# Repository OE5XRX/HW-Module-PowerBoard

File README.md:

# HW-Module-PowerBoard

## License

This project is licensed under [CERN-OHL-S-2.0](https://choosealicense.com/licenses/cern-ohl-s-2.0/).

## Badges

<br>
<br>
<br>
<br>
<br>

## Contact

OE5XRX Amateur Radio Club<br>
🌐 https://oe5xrx.org<br>
✉️ info@oe5xrx.org<br>

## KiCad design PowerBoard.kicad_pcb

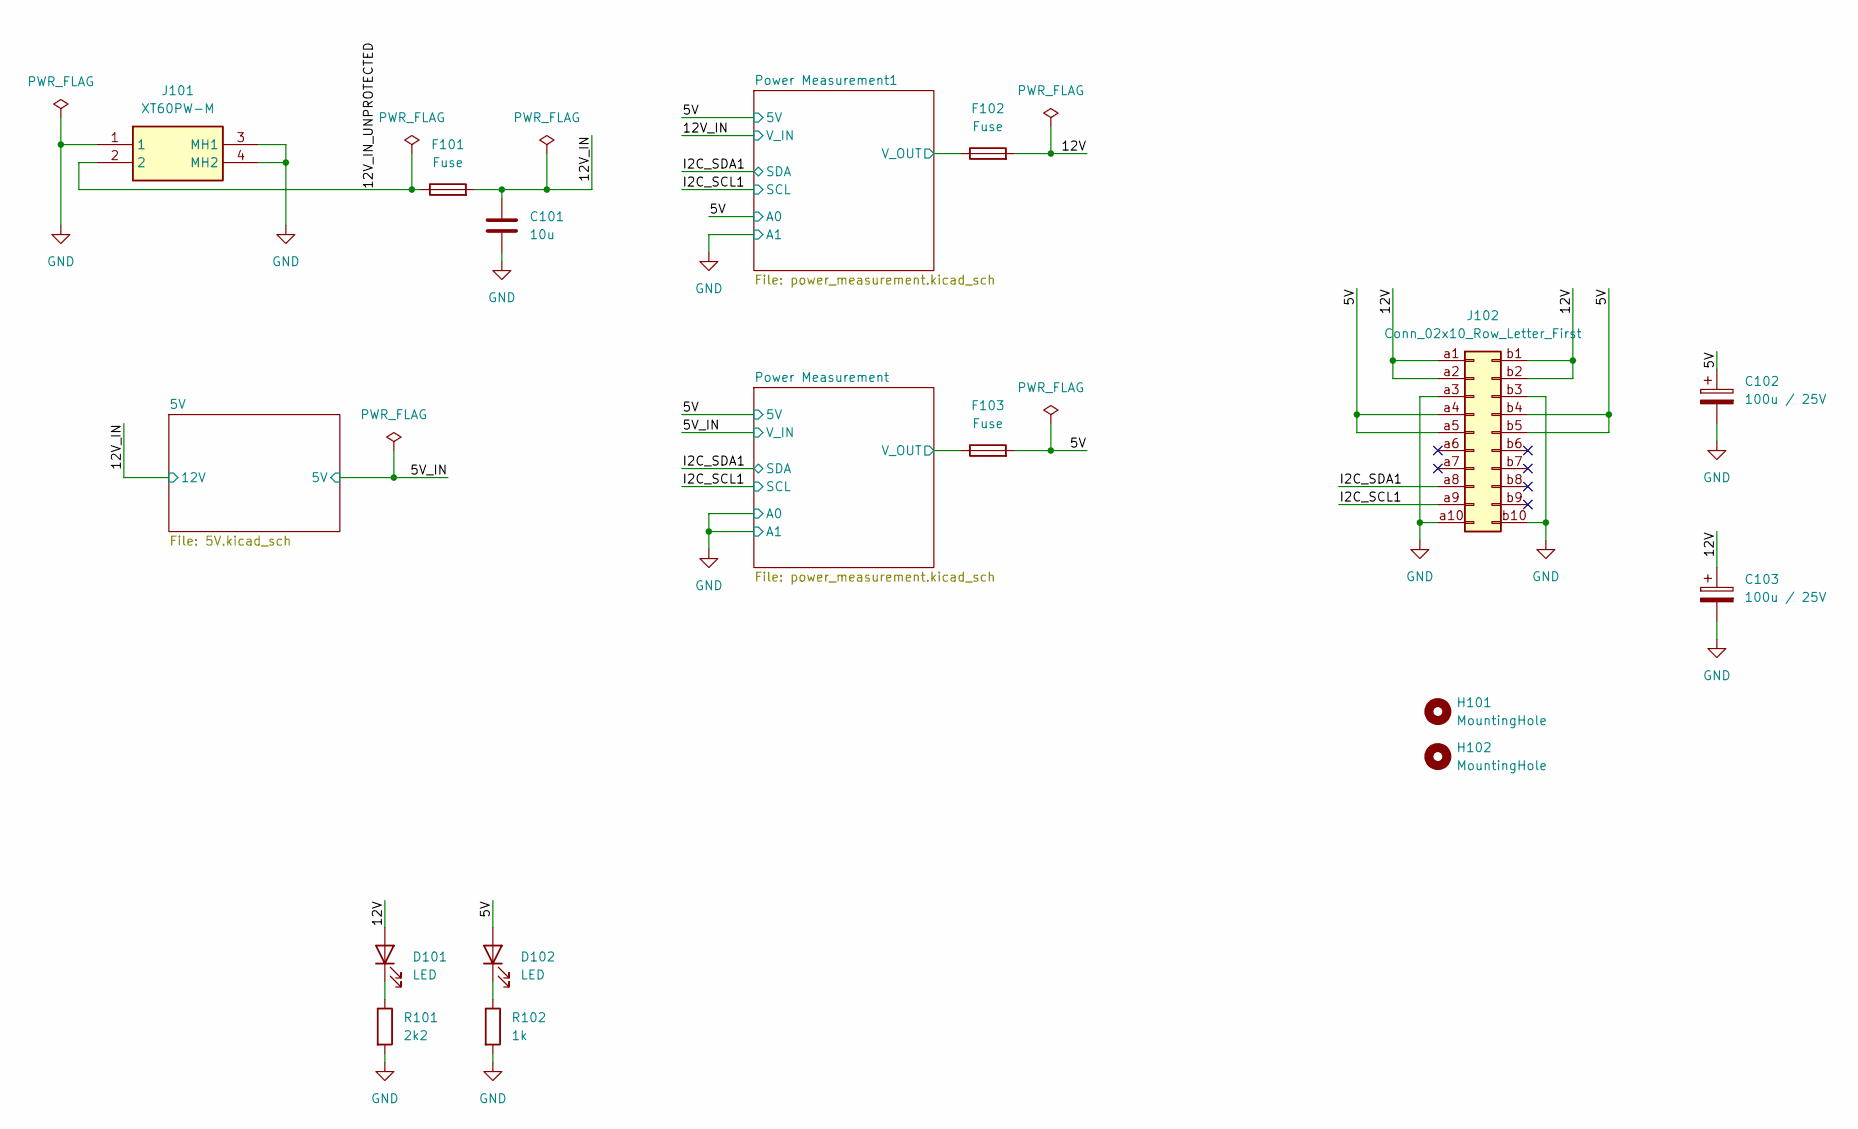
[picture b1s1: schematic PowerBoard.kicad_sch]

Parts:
C101: 10u; C_1206_3216Metric; LCSC C13585
C102, C103: 100u / 25V; CP_EIA-7343-43_Kemet-X; LCSC C132558
D101, D102: LED; LED_0805_2012Metric; LCSC C84256
F101, F102, F103: Fuse; FUSE_01530007Z; MOUSER 576-01530007Z
H101, H102: MountingHole; MountingHole_3.2mm_M3
J101: XT60PW-M; XT60PWM
J102: Conn_02x10_Row_Letter_First; PCN10C-20S-2.54DS; MOUSER 798-PCN10C20S254DS72
R101: 2k2; R_0805_2012Metric; LCSC C17520
R102: 1k; R_0805_2012Metric; LCSC C17513

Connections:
/5V: C102.1, D102.2 (A), F103.2, J102.a4, J102.a5, J102.b4, J102.b5; also elsewhere on the board
/12V: C103.1, D101.2 (A), F102.2, J102.a1, J102.a2, J102.b1, J102.b2
/12V_IN: C101.1, F101.2; also elsewhere on the board
/12V_IN_UNPROTECTED: F101.1, J101.2
/I2C_SCL1: J102.a9; also elsewhere on the board
/I2C_SDA1: J102.a8; also elsewhere on the board
/Power Measurement1/V_OUT: F102.1; also elsewhere on the board
/Power Measurement/V_OUT: F103.1; also elsewhere on the board
GND: C101.2, C102.2, C103.2, J101.1, J101.3 (MH1), J101.4 (MH2), J102.a3, J102.a10, J102.b3, J102.b10, R101.2, R102.2; also elsewhere on the board
unnamed: D101.1 (K), R101.1
unnamed: D102.1 (K), R102.1

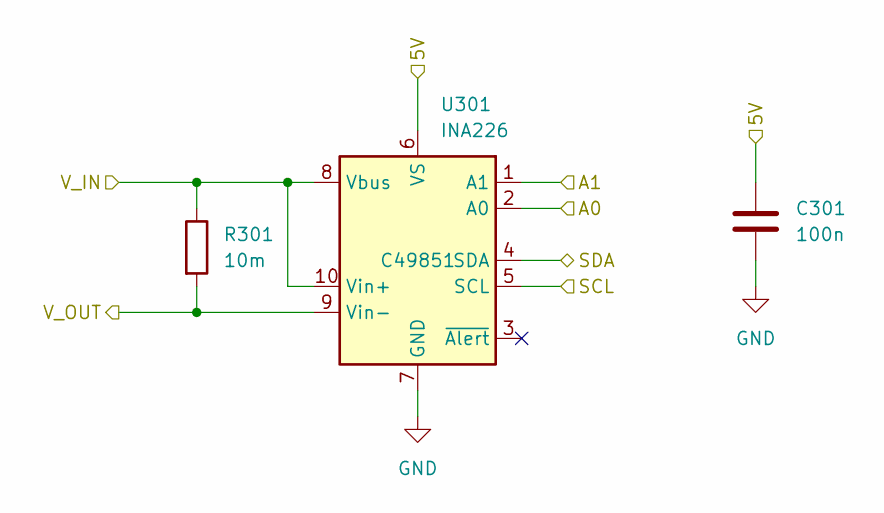
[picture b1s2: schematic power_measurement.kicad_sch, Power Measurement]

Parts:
C301: 100n; C_0805_2012Metric; LCSC C28233
R301: 10m; R_2512_6332Metric; MOUSER 652-CRF2512FZR010ELF
U301: INA226; VSSOP-10_3x3mm_P0.5mm; LCSC C49851

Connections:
/5V: C301.1, U301.6 (VS); also elsewhere on the board
/5V_IN: R301.1, U301.8 (Vbus), U301.10 (Vin+); also elsewhere on the board
/I2C_SCL1: U301.5 (SCL); also elsewhere on the board
/I2C_SDA1: U301.4 (SDA); also elsewhere on the board
/Power Measurement/V_OUT: R301.2, U301.9 (Vin-); also elsewhere on the board
GND: C301.2, U301.1 (A1), U301.2 (A0), U301.7 (GND); also elsewhere on the board

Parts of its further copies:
C401: 100n; C_0805_2012Metric; LCSC C28233
R401: 10m; R_2512_6332Metric; MOUSER 652-CRF2512FZR010ELF
U401: INA226; VSSOP-10_3x3mm_P0.5mm; LCSC C49851

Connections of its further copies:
/5V: C401.1, U401.2 (A0), U401.6 (VS); also elsewhere on the board
/12V_IN: R401.1, U401.8 (Vbus), U401.10 (Vin+); also elsewhere on the board
/I2C_SCL1: U401.5 (SCL); also elsewhere on the board
/I2C_SDA1: U401.4 (SDA); also elsewhere on the board
/Power Measurement1/V_OUT: R401.2, U401.9 (Vin-); also elsewhere on the board
GND: C401.2, U401.1 (A1), U401.7 (GND); also elsewhere on the board

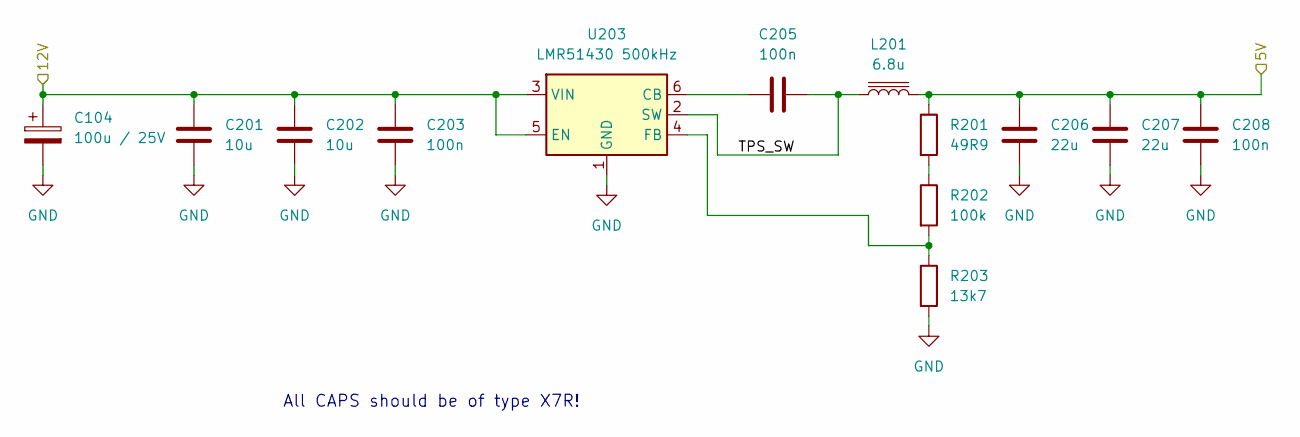
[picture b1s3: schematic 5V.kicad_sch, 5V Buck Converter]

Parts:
C104: 100u / 25V; CP_EIA-7343-43_Kemet-X; LCSC C132558
C201, C202: 10u; C_1206_3216Metric; LCSC C13585
C203, C205, C208: 100n; C_0805_2012Metric; LCSC C28233
C206, C207: 22u; C_1206_3216Metric; LCSC C12891
L201: 6.8u; WE-XHMI_6060; MOUSER 710-74439346068
R201: 49R9; R_0805_2012Metric; MOUSER 667-ERA-6AED49R9V
R202: 100k; R_0805_2012Metric; MOUSER 603-RC0805JR-07100KL
R203: 13k7; R_0805_2012Metric; MOUSER 652-CR0805FX-1372ELF
U203: LMR51430 500kHz; SOT-23-6; MOUSER 595-LMR51430XDDCR

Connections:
/5V/TPS_SW: C205.2, L201.1, U203.2 (SW)
/5V_IN: C206.2, C207.2, C208.2, L201.2, R201.1; also elsewhere on the board
/12V_IN: C104.1, C201.1, C202.1, C203.1, U203.3 (VIN), U203.5 (EN); also elsewhere on the board
GND: C104.2, C201.2, C202.2, C203.2, C206.1, C207.1, C208.1, R203.2, U203.1 (GND); also elsewhere on the board
unnamed: R201.2, R202.1
unnamed: C205.1, U203.6 (CB)
unnamed: R202.2, R203.1, U203.4 (FB)

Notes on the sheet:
All CAPS should be of type X7R!

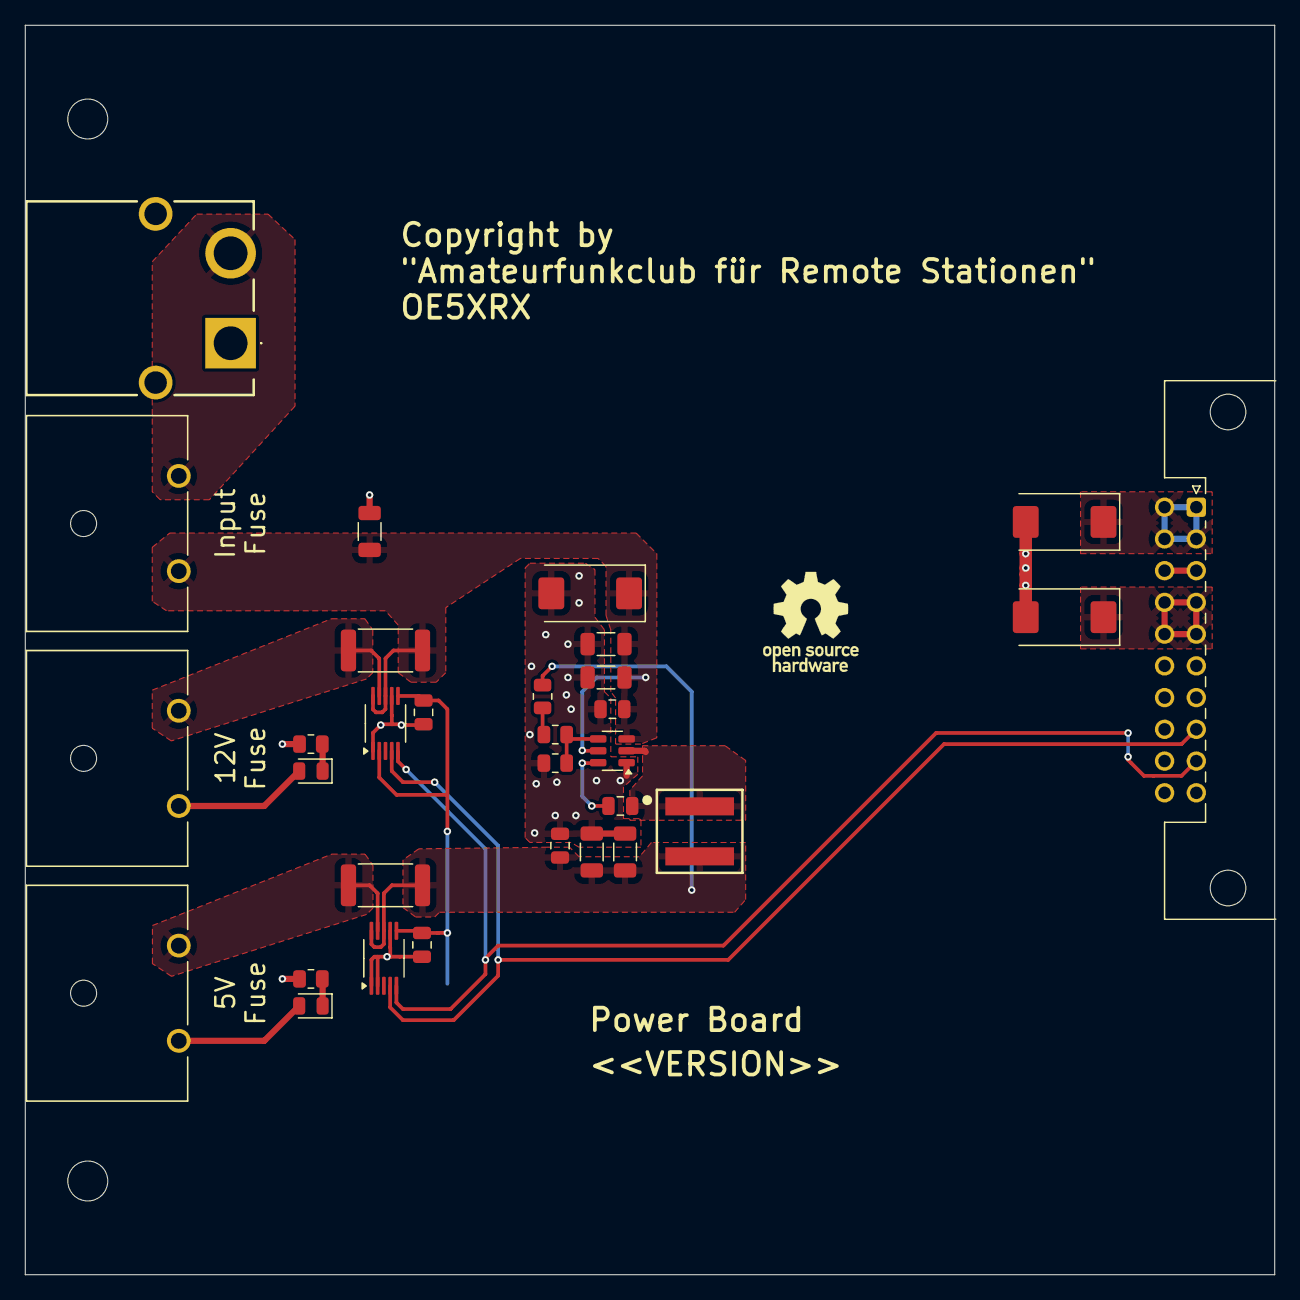
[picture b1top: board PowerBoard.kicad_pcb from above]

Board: 4 copper layers, 100.0 x 100.0 mm, 33 parts (0 on the bottom side), 16 nets.

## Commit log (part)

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2025-08-27 setup project
2025-08-28 fix path for external components
2025-08-28 fix index
2025-09-05 🔄 created local 'doc/_config.yml' from remote 'doc/_config.yml'
2025-09-05 🔄 created local 'doc/favicon.ico' from remote 'doc/favicon.ico'
2025-09-05 🔄 synced local '.github/workflows/create-debug-docs.yaml' with remote '.github/workflows/create-debug-docs.yaml'
2025-09-05 🔄 created local 'Gemfile' from remote 'Gemfile'
2025-09-05 Initial gh-pages commit
2025-09-05 Deploying to gh-pages from @ OE5XRX/HW-Module-PowerBoard@147898b77bba4ee0519c7e8ac76ab752825e97f0 🚀
2026-05-12 refactor(ci): replace workflows with HW-Module-CI thin wrappers
2026-05-12 chore(ci): delete files now provided by HW-Module-CI
2026-05-12 feat(docs): migrate index.md to Jekyll Liquid for output paths
2026-05-12 chore: ignore CI-generated doc/_data/project.yml
2026-05-12 rename(kicad): main.kicad_* → PowerBoard.kicad_*
2026-05-12 Deploying to gh-pages from @ OE5XRX/HW-Module-PowerBoard@edb127a616a350726788fd26fe98536b4139deb3 🚀
2026-05-12 Deploying to gh-pages from @ OE5XRX/HW-Module-PowerBoard@7f9eb825cc38174e3f664904ce8a251a15ba0276 🚀
2026-05-12 docs: rewrite Power index.md with overview, block-diagram, INA226 ranges, bringup
    Adds:
    - 1-sentence description front-matter (SEO + just-the-docs side-nav)
    - Übersicht paragraph linking to BusBoard and CM4Carrier
    - Mermaid block-diagram of the +12V/+5V flow
    - Versorgung table (input, +12V passthrough, +5V buck)
    - I²C measurement table with computed full-scale current and resolution
2026-05-12 ci: retrigger kibot-check with HW-Module-CI@main containing Docker-direct fix
2026-05-12 ci: retrigger after HW-Module-CI image pin to 1.8.5-7_k9.0.7
2026-05-12 Deploying to gh-pages from @ OE5XRX/HW-Module-PowerBoard@8464c7f8df2162f6445a5081175db85468c06fd6 🚀
2026-05-13 fix(docs): INA226 Strom-Auflösung ist konfigurierbar, nicht 125 µA/LSB
    Copilot-Review-Befund auf PR #6 (L54): Der Wert '125 µA/LSB' war falsch
    hergeleitet (VShunt-LSB durch Shunt-Widerstand geteilt → ergibt nicht
    die Current-Register-Auflösung).
    Die INA226 Strom-Auflösung wird über das CALIBRATION-Register
    festgelegt: Current_LSB = max_expected_current / 32768. Bei 8 A
    Vollausschlag wäre das ≈250 µA/LSB; der Wert ist treiberabhängig
2026-05-13 Deploying to gh-pages from @ OE5XRX/HW-Module-PowerBoard@6f19d5ca98f6ddafb982a2fba1658a9fd8a10f9b 🚀
2026-05-15 Deploying to gh-pages from @ OE5XRX/HW-Module-PowerBoard@b89be9ff7d38395539683d776c3b683414651c10 🚀
2026-05-15 Deploying to gh-pages from @ OE5XRX/HW-Module-PowerBoard@9e7ef48cee8d4e6c6792b3212eb766d0ac225ed4 🚀
2026-05-15 Deploying to gh-pages from @ OE5XRX/HW-Module-PowerBoard@be7951748d1fc851503a46f0d741df102d1b80f4 🚀

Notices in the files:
PowerBoard.kicad_pcb:
Copyright by
{dblquote}Amateurfunkclub für Remote Stationen{dblquote}
README.md:
License: CERN-OHL-S
